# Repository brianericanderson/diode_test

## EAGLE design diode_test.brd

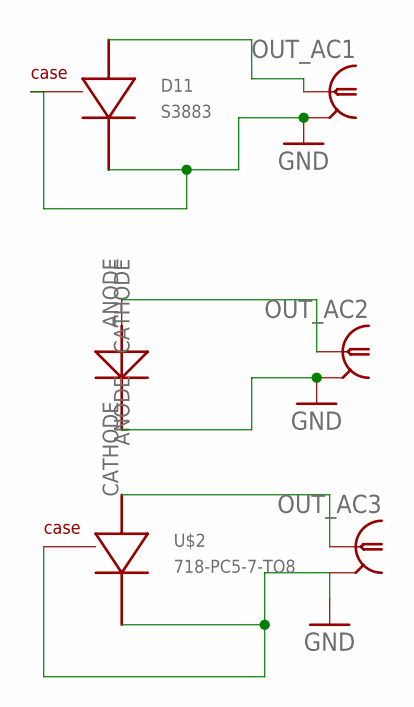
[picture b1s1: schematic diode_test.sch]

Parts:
D11: S3883; S3883-CASE
OUT_AC1, OUT_AC2, OUT_AC3: BNC-H; BNC90
U$1: 718-PC5-7-TO5
U$2: 718-PC5-7-TO8

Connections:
GND: D11.CASE, D11.CATHODE, OUT_AC1.2, OUT_AC2.2, OUT_AC3.2, U$1.CATHODE, U$2.CASE, U$2.CATHODE
unnamed: D11.ANODE, OUT_AC1.1
unnamed: OUT_AC2.1, U$1.ANODE
unnamed: OUT_AC3.1, U$2.ANODE

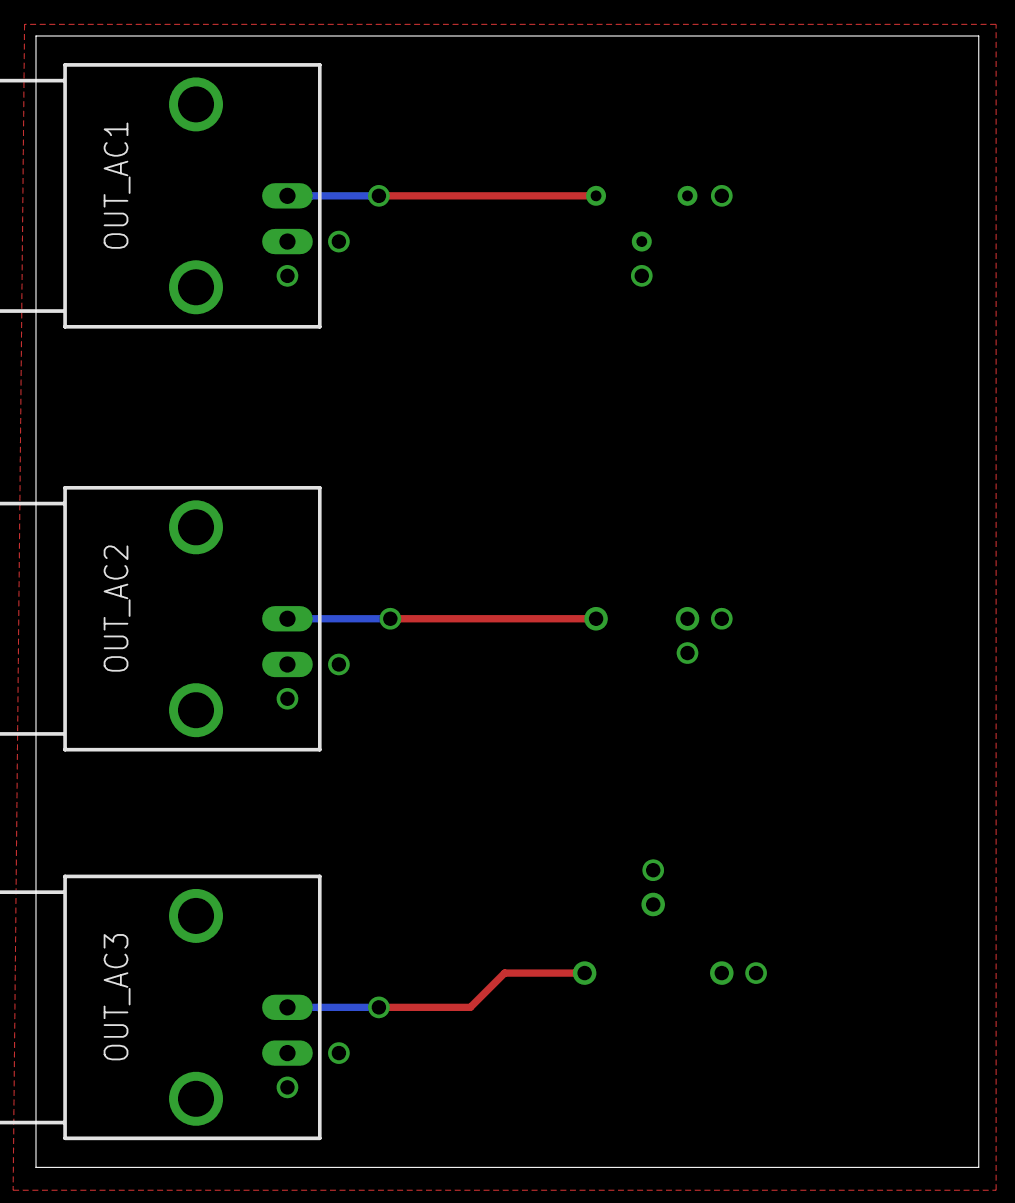
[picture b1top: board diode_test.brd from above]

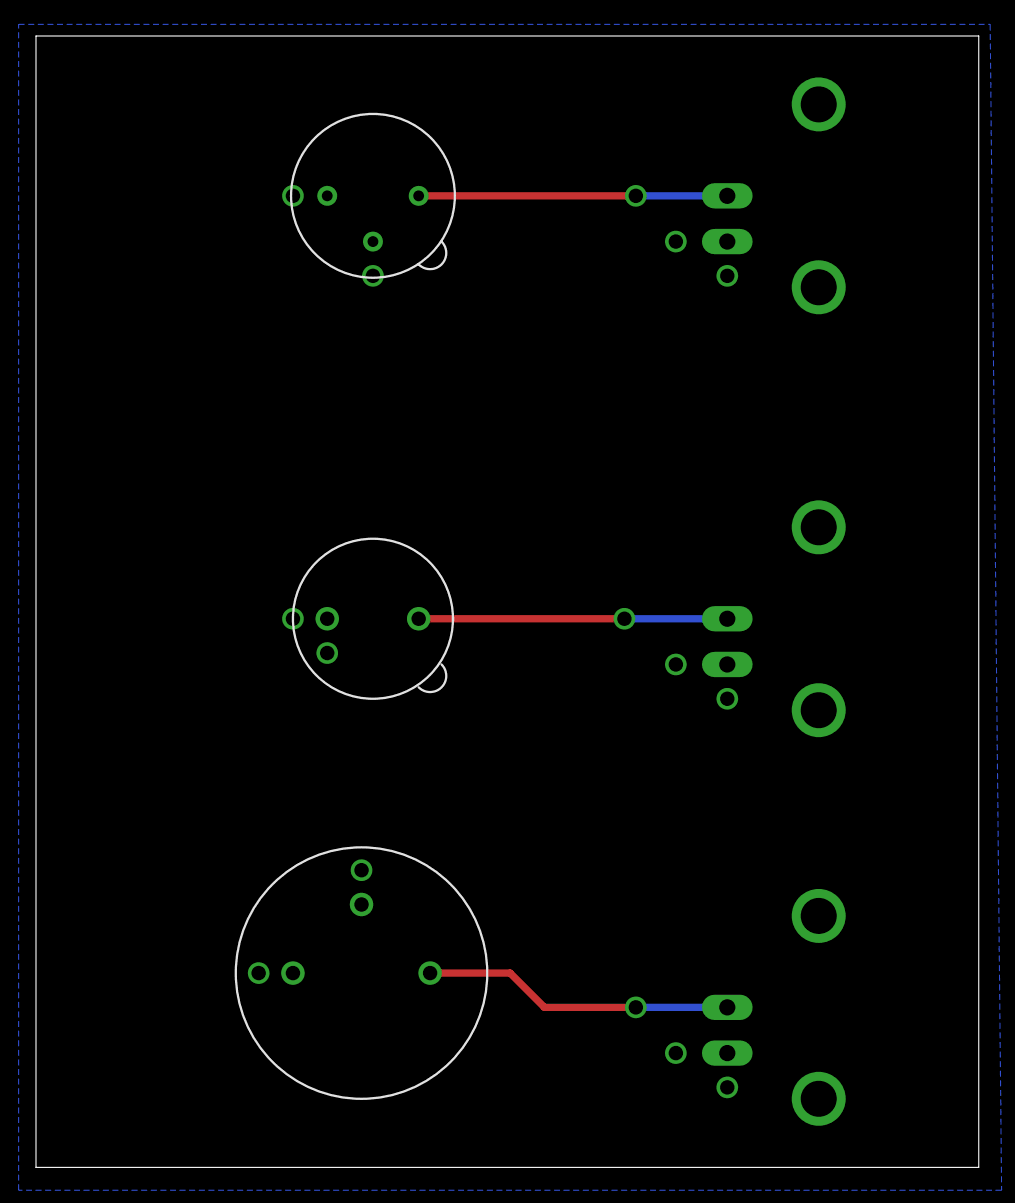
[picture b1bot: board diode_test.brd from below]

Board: 2 copper layers, 52.4 x 62.9 mm, 6 parts (3 on the bottom side), 4 nets.

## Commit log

2017-05-09 first pass
